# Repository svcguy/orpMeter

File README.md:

# orpMeter
## A basic combination pH/ORP(redox) probe electrometer circuit
This is a simple analog front end (AFE), ADC, isolated DC-DC, and SPI isolator circuit to interface to a standard combination pH or ORP probe.

## Circuit Theory of Operation
### AFE
(coming soon)

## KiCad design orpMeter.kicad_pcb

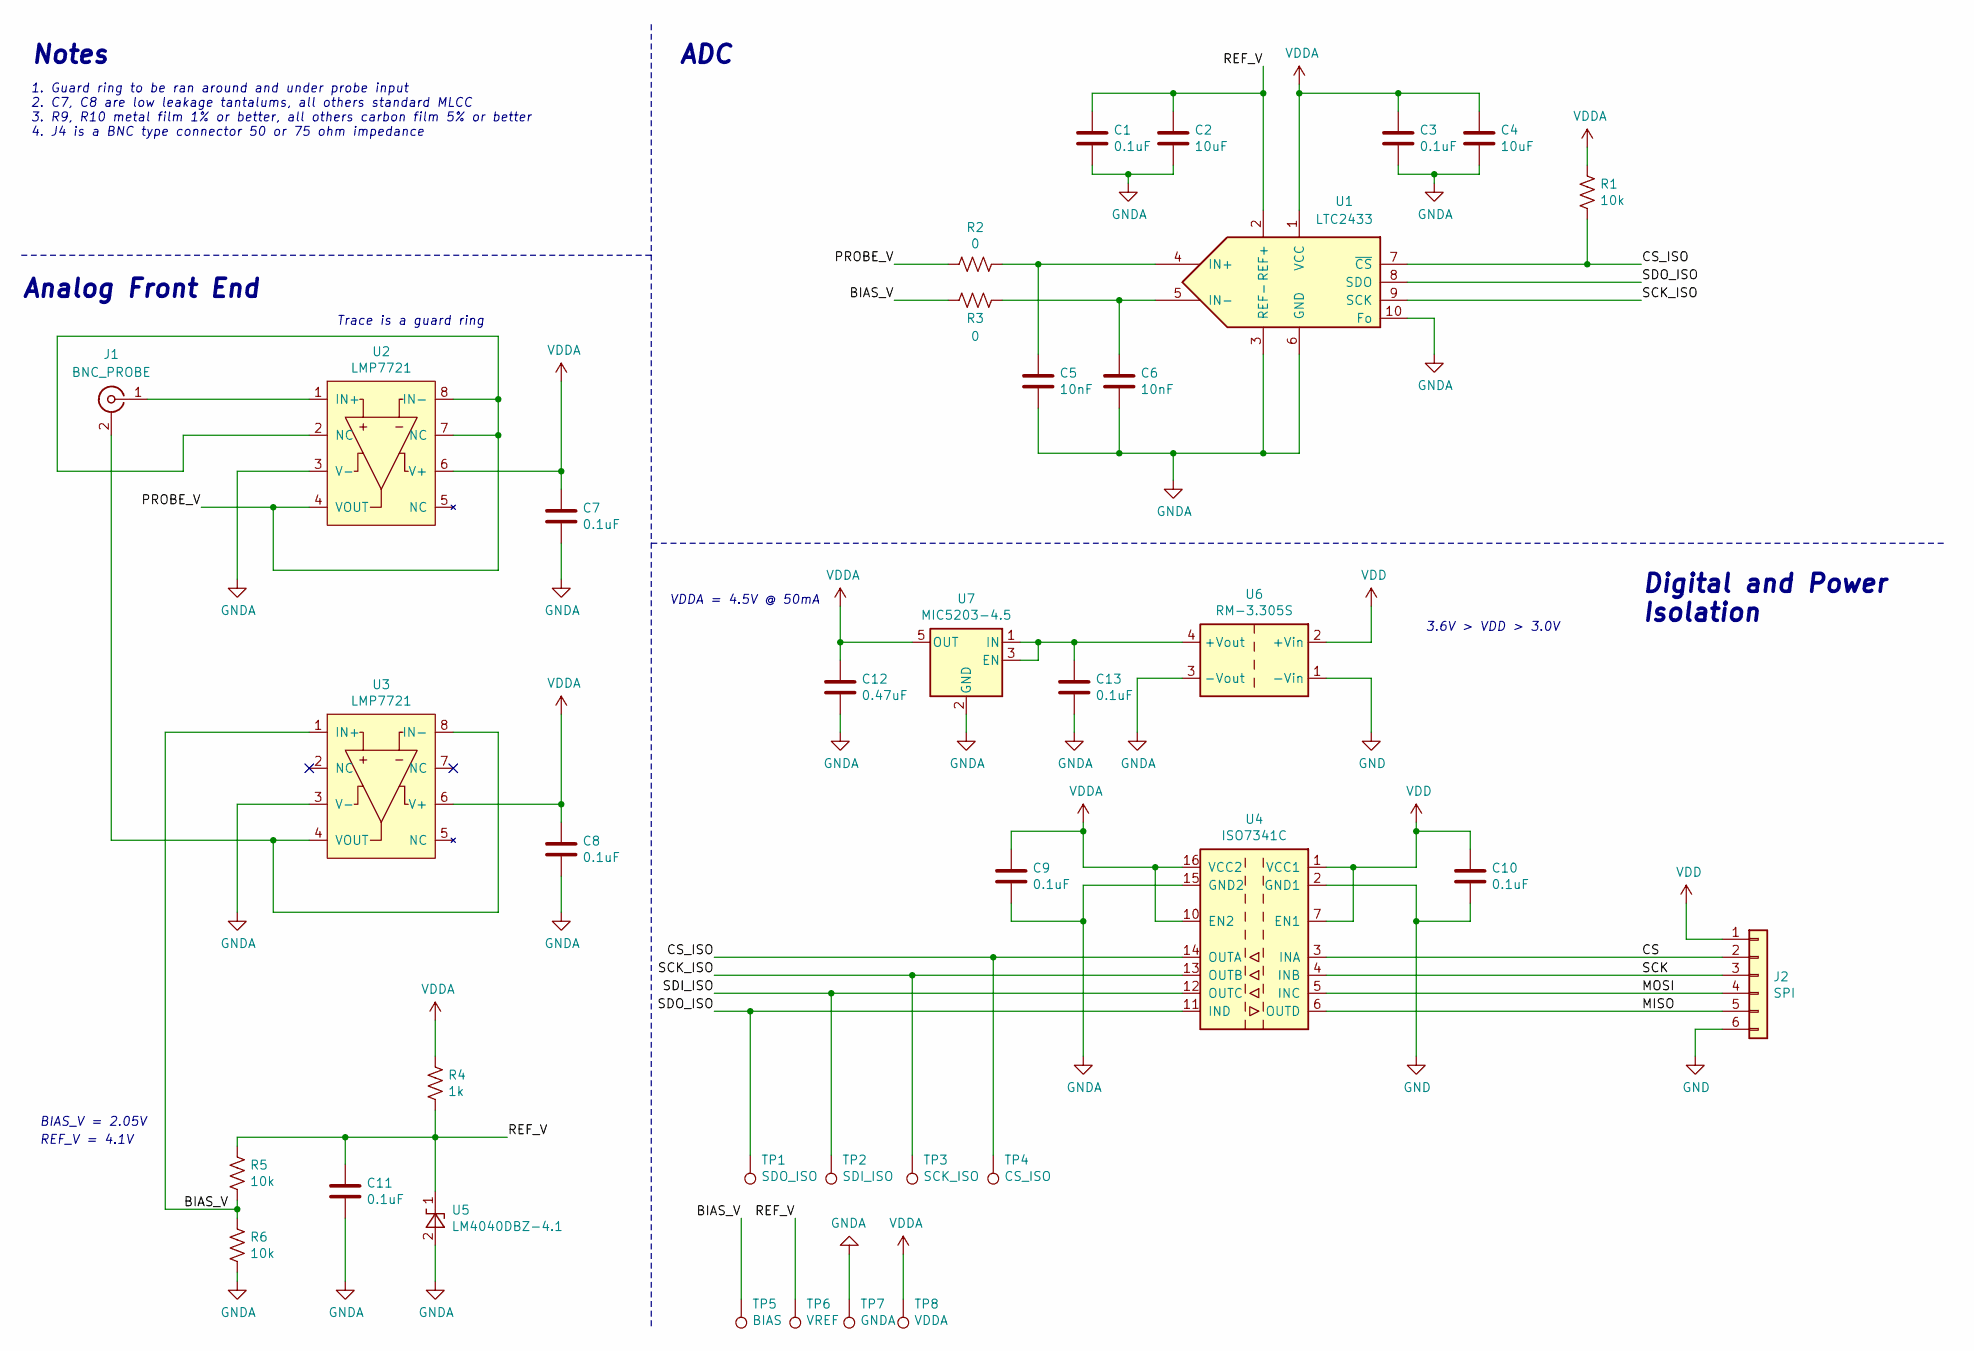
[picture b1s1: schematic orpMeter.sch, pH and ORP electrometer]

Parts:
C1, C3, C9, C10, C13: 0.1uF; C_0603_1608Metric; Digikey 478-3540-1-ND
C2, C4: 10uF; CP_EIA-2012-15_AVX-P
C5, C6: 10nF; C_0603_1608Metric; Digikey 399-17880-1-ND
C7, C8, C11: 0.1uF; CP_EIA-2012-15_AVX-P; Digikey 478-11592-1-ND
C12: 0.47uF; C_0603_1608Metric; Digikey 399-4922-1-ND
J1: BNC_PROBE; BNC_Amphenol_B6252HB-NPP3G-50_Horizontal; Digikey A24485-ND
J2: SPI; PinHeader_1x06_P2.54mm_Vertical; Digikey DNP
R1, R5, R6: 10k; R_0603_1608Metric; Digikey 2019-RN73H1JTTD1002B50CT-ND
R2, R3: 0; R_0603_1608Metric; Digikey 541-4013-1-ND
R4: 1k; C_0603_1608Metric; Digikey RMCF0603FG1K00CT-ND
TP1: SDO_ISO; TestPoint_Pad_2.0x2.0mm; Digikey DNP
TP2: SDI_ISO; TestPoint_Pad_2.0x2.0mm; Digikey DNP
TP3: SCK_ISO; TestPoint_Pad_2.0x2.0mm; Digikey DNP
TP4: CS_ISO; TestPoint_Pad_2.0x2.0mm; Digikey DNP
TP5: BIAS; TestPoint_Pad_2.0x2.0mm; Digikey DNP
TP6: VREF; TestPoint_Pad_2.0x2.0mm; Digikey DNP
TP7: GNDA; TestPoint_Pad_2.0x2.0mm; Digikey DNP
TP8: VDDA; TestPoint_Pad_2.0x2.0mm; Digikey DNP
U1: LTC2433; MSOP-10_3x3mm_P0.5mm; Digikey LTC2433-1CMS#PBF-ND
U2, U3: LMP7721; SOIC-8_3.9x4.9mm_P1.27mm; Digikey LMP7721IMA/NOPB-ND
U4: ISO7341C; SOIC-16W_7.5x10.3mm_P1.27mm; Digikey 296-47779-1-ND
U5: LM4040DBZ-4.1; SOT-23; Digikey LM4040DIM3-4.1/NOPBCT-ND
U6: RM-3.305S; Converter_DCDC_Murata_MEE1SxxxxSC_THT; Digikey 945-1518-5-ND
U7: MIC5203-4.5; SOT-23-5; Digikey MIC5203-4.5YM5-CT-ND

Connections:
/BIAS_V: R3.2, R5.2, R6.1, TP5.1, U3.1 (IN+)
/CS: J2.2, U4.3 (INA)
/CS_ISO: R1.2, TP4.1, U1.7 (~CS), U4.14 (OUTA)
/MISO: J2.5, U4.6 (OUTD)
/MOSI: J2.4, U4.5 (INC)
/PROBE_V: R2.2, U2.2 (NC), U2.4 (VOUT), U2.7 (NC), U2.8 (IN-)
/REF_V: C1.1, C2.1, C11.1, R4.2, R5.1, TP6.1, U1.2 (REF+), U5.1 (K)
/SCK: J2.3, U4.4 (INB)
/SCK_ISO: TP3.1, U1.9 (SCK), U4.13 (OUTB)
/SDI_ISO: TP2.1, U4.12 (OUTC)
/SDO_ISO: TP1.1, U1.8 (SDO), U4.11 (IND)
GND: C10.2, J2.6, U4.2 (GND1), U4.8 (GND1), U6.1 (-Vin)
GNDA: C1.2, C2.2, C3.2, C4.2, C5.2, C6.2, C7.2, C8.2, C9.2, C11.2, C12.2, C13.2, R6.2, TP7.1, U1.3 (REF-), U1.6 (GND), U1.10 (Fo), U2.3 (V-), U3.3 (V-), U4.9 (GND2), U4.15 (GND2), U5.2 (A), U6.3 (-Vout), U7.2 (GND)
unnamed: C5.1, R2.1, U1.4 (IN+)
unnamed: C6.1, R3.1, U1.5 (IN-)
unnamed: C13.1, U6.4 (+Vout), U7.1 (IN), U7.3 (EN)
unnamed: J1.1 (In), U2.1 (IN+)
unnamed: J1.2 (Ext), U3.4 (VOUT), U3.8 (IN-)
VDD: C10.1, J2.1, U4.1 (VCC1), U4.7 (EN1), U6.2 (+Vin)
VDDA: C3.1, C4.1, C7.1, C8.1, C9.1, C12.1, R1.1, R4.1, TP8.1, U1.1 (VCC), U2.6 (V+), U3.6 (V+), U4.10 (EN2), U4.16 (VCC2), U7.5 (OUT)

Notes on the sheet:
BIAS_V = 2.05V
Trace is a guard ring
REF_V = 4.1V
3.6V > VDD > 3.0V
VDDA = 4.5V @ 50mA
Analog Front End
ADC
Digital and Power Isolation
Notes
1. Guard ring to be ran around and under probe input 2. C7, C8 are low leakage tantalums, all others standard MLCC 3. R9, R10 metal film 1% or better, all others carbon film 5% or better 4. J4 is a BNC type connector 50 or 75 ohm impedance

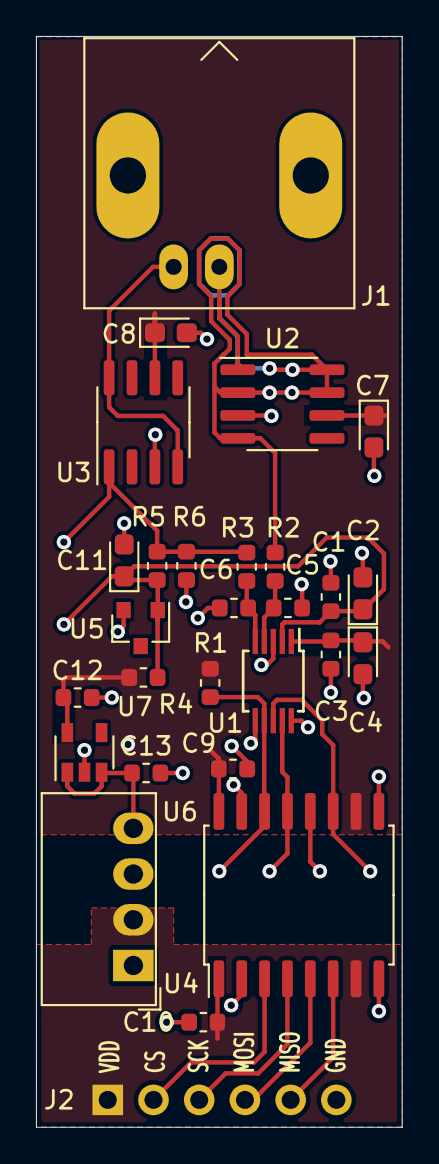
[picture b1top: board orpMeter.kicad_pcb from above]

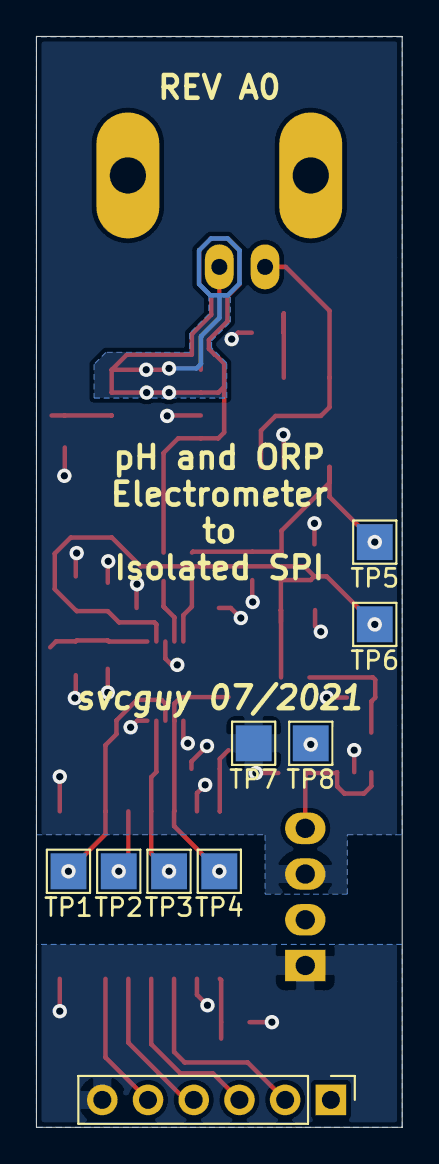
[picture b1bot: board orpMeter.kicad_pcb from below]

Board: 2 copper layers, 20.3 x 60.6 mm, 36 parts (9 on the bottom side), 20 nets.

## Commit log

2021-10-19 Initial commit REVA0
2021-10-19 Add README
